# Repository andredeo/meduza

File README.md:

# meduZa
Segue a descrição dos arquivos:
  - **meduZa.brd:** Layout da placa (circuito impresso)
  - **meduZa.ino:** Códigos Arduino a serem carregados no Arduino Mega
  - **meduZa.pdf:** Esquemático da placa
  - **meduZa.py:** Códigos em Python para interagir com os sensores e enviar os dados para o servidor Zabbix
  - **meduZa.sch:** Esquemático da placa
  - **Template Zabbix IoT - meduZa:** Template para o Zabbix com os itens da meduZa
  - **Template Zabbix IoT - RSSI:** Template para o Zabbix com os itens de RSSI

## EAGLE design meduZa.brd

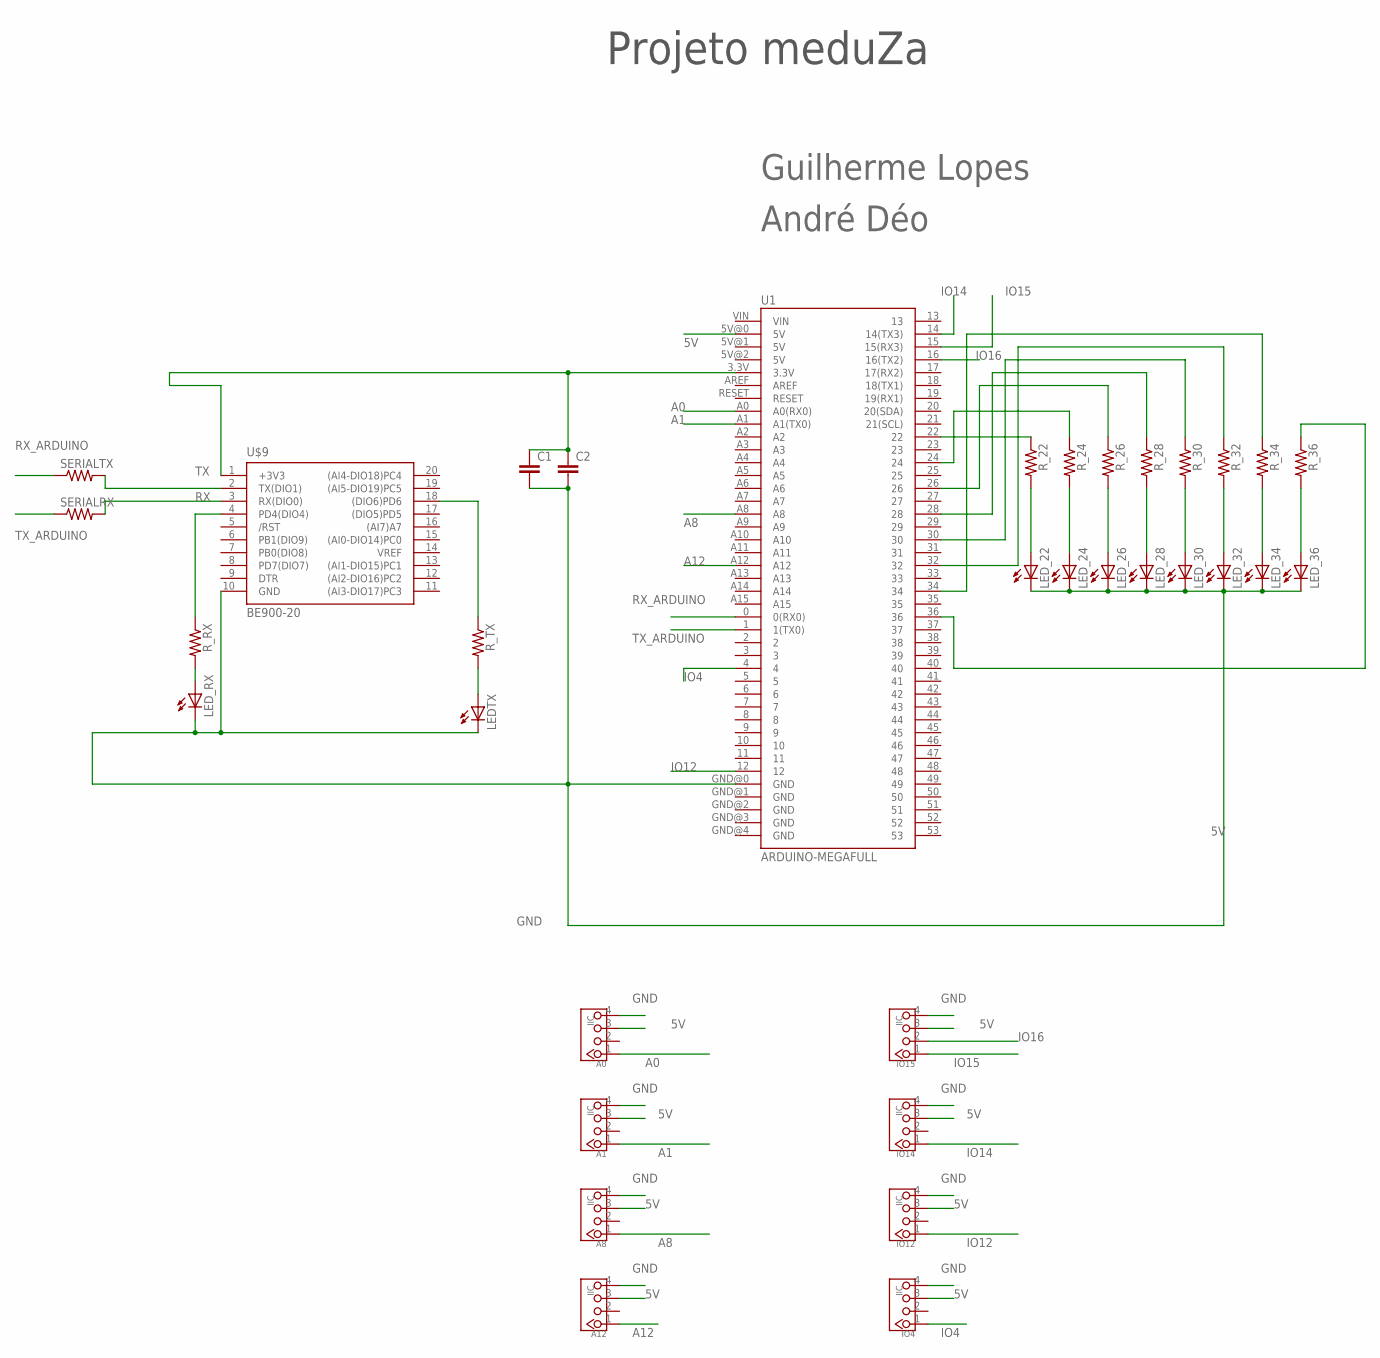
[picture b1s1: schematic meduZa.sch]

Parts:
A0, A1, A8, A12: IIC; 4P-2.0
C1, C2: 0.1UF-50V-20%(PTH)KIT-EZ; CAP-PTH-SMALL-KIT
IO4, IO12, IO14, IO15: IIC; 4P-2.0
LEDTX: LED5MM
LED_22, LED_24, LED_26, LED_28, LED_30, LED_32, LED_34, LED_36: LED5MM
LED_RX: LED5MM
R_22, R_24, R_26, R_28, R_30, R_32, R_34, R_36: R-US_0204/7; 0204/7
R_RX: R-US_0204/7; 0204/7
R_TX: R-US_0204/7; 0204/7
SERIALRX: R-US_0204/7; 0204/7
SERIALTX: R-US_0204/7; 0204/7
U1: ARDUINO-MEGAFULL; ARDUINO_MEGA
U$9: BE900-20; BE900_20

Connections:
3V3: C1.1, C2.1, U1.3.3V, U$9.1 (+3V3)
5V: A0.3, A1.3, A8.3, A12.3, IO4.3, IO12.3, IO14.3, IO15.3, U1.5V@0 (5V)
A0: A0.1, U1.A0 (A0(RX0))
A1: A1.1, U1.A1 (A1(TX0))
A8: A8.1, U1.A8
A12: A12.1, U1.A12
GND: A0.4, A1.4, A8.4, A12.4, C1.2, C2.2, IO4.4, IO12.4, IO14.4, IO15.4, LEDTX.K (C), LED_22.K (C), LED_24.K (C), LED_26.K (C), LED_28.K (C), LED_30.K (C), LED_32.K (C), LED_34.K (C), LED_36.K (C), LED_RX.K (C), U1.GND@0 (GND), U$9.10 (GND)
IO4: IO4.1, U1.4
IO12: IO12.1, U1.12
IO14: IO14.1, U1.14 (14(TX3))
IO15: IO15.1, U1.15 (15(RX3))
IO16: IO15.2, U1.16 (16(TX2))
unnamed: R_RX.1, U$9.4 (PD4(DIO4))
unnamed: R_TX.1, U$9.18 ((DIO6)PD6)
unnamed: LED_22.A, R_22.2
unnamed: LED_24.A, R_24.2
unnamed: LED_RX.A, R_RX.2
unnamed: LEDTX.A, R_TX.2
unnamed: LED_26.A, R_26.2
unnamed: LED_28.A, R_28.2
unnamed: LED_30.A, R_30.2
unnamed: LED_32.A, R_32.2
unnamed: LED_34.A, R_34.2
unnamed: LED_36.A, R_36.2
unnamed: R_22.1, U1.22
unnamed: R_24.1, U1.24
unnamed: R_26.1, U1.26
unnamed: R_28.1, U1.28
unnamed: R_30.1, U1.30
unnamed: R_32.1, U1.32
unnamed: R_34.1, U1.34
unnamed: R_36.1, U1.36
RX: SERIALRX.2, U$9.3 (RX(DIO0))
RX_ARDUINO: SERIALTX.1, U1.0 (0(RX0))
TX: SERIALTX.2, U$9.2 (TX(DIO1))
TX_ARDUINO: SERIALRX.1, U1.1 (1(TX0))

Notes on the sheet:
Projeto meduZa
Guilherme Lopes
André Déo

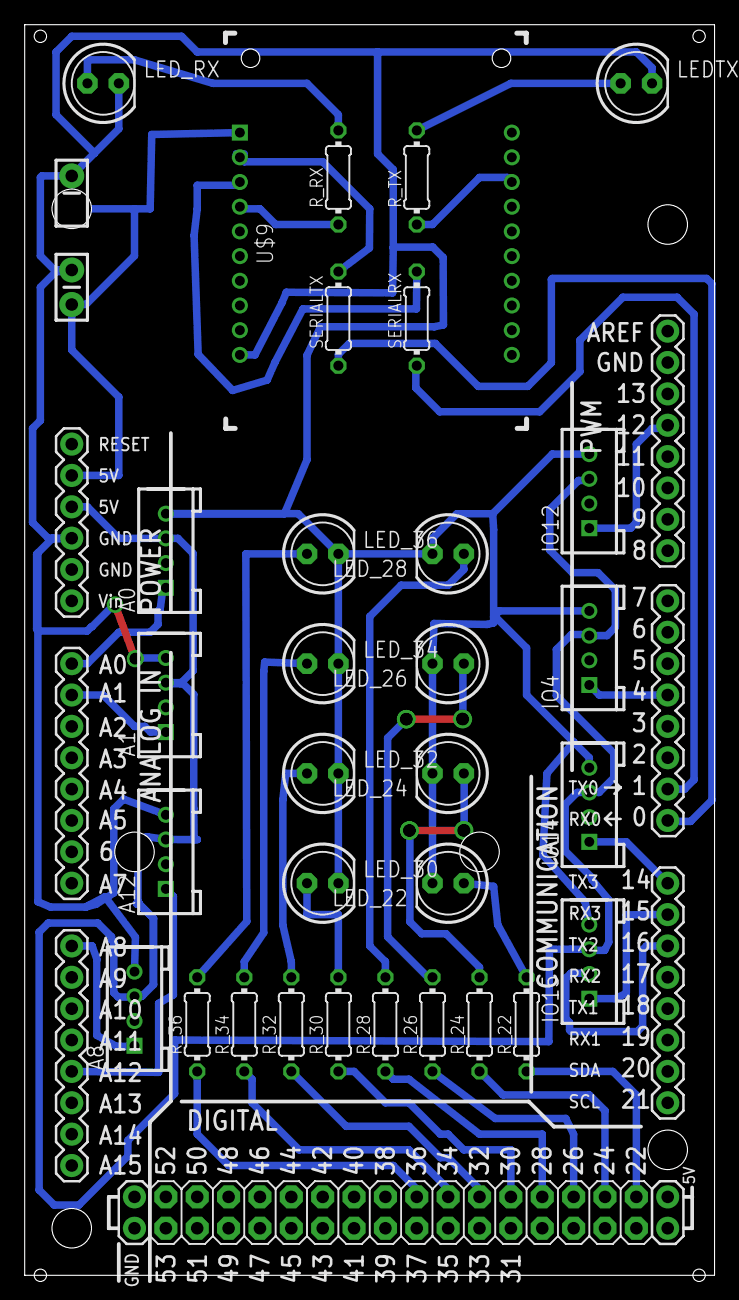
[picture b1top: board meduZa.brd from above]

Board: 2 copper layers, 55.9 x 101.3 mm, 34 parts (0 on the bottom side), 36 nets.

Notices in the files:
parts and their libraries:
SparkFun-Boards: Licensing: Creative Commons ShareAlike 4.0 International - https://creativecommons.org/licenses/by-sa/4.0
